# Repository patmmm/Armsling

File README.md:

About
=====

This is a "simple", but complete example of how to utilize WebRTC to do peer to
peer voice and video chatting between two or more people.

### Server Side 
This example uses node.js and socket.io to create a "Signaling Server", which
runs on (or near) your web server to manage who should talk to who. The purpose
of the signaling server is to relay information between peers while you are
setting them up to talk directly to each other.

### Client Side
Included is `client.html` which contains all of the logic to connect to the
signaling server, join a virtual group chat channel, connect with peers, and
stream video and audio to all party members using the raw WebRTC API.

Running
=======

### Node.js signaling server
You'll need to install `node.js` as well as the `express` and `socket.io` libraries:
```
npm install -g socket.io express
```

Then simply run the signaling server:
```
node signaling-server.js
```

### Web server
You'll also probably want to host `client.html` on a web server somewhere. You'll need
to edit `client.html` and change `YOURSERVERNAMEHERE` to be the hostname or IP of 
the signaling server.

Note: you can also simply open the file locally instead of using a web server,
but at the time of writing this only firefox will let you access the
webcam/microphone from a file hosted off of your local machine.

### Running the sample
Now navigate to wherever you stuck `client.html` and you should be presented with
a dialog asking permission to access your microphone / webcam. Once accepted,
you should see a local stream appear on the page. Now open up the same page in
another browser, on the same computer or another, and watch as the magic of WebRTC takes
effect and both images and audio samples mysteriously move from one browser to the other.
Repeat with as many browsers as you dare.

Note: At the time of writing this, only firefox and chrome support WebRTC,
however both browsers support this on Windows, Linux, Mac, and Android, so lots
of fun can be had pointing everyones' phones, tablets, and laptops at that `client.html`
and bogging down your network with audio/video traffic.

Using things other than jQuery, node.js, and socket.io
=============================================
The choice of node.js and socket.io is based purely on my familiarity with them
and the fact that their fairly easy to understand even if you aren't familiar
with them. However, you can use any mechanisms you want for your signaling system, you
just need a way to exchange ICE candidates and session descriptions between
clients.

The use of jQuery is even less important, I just like using it for DOM
manipulation, and we only do that to add and remove the <video>/<audio>
elements in this demo. We don't use it at all for anything WebRTC specific in
this example.

Adapter.js
==========
You'll see `client.html` use `adapter.js`. This "library" just normalizes the
WebRTC API, which will only be necessary while WebRTC is making its way through
the standards process. Once everything is standardized and functions are
de-prefixed in the browsers, this won't be necessary anymore.
# Armsling

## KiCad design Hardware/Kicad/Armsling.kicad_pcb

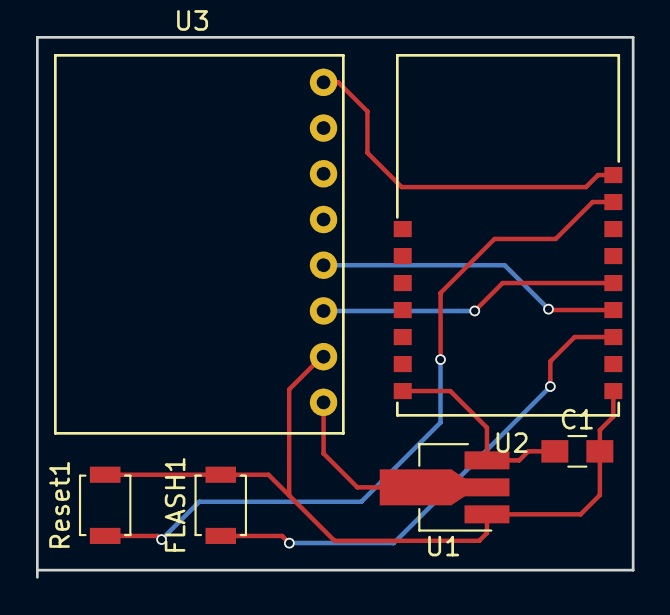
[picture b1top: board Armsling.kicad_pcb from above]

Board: 2 copper layers, 33.1 x 30.0 mm, 6 parts (0 on the bottom side), 8 nets.

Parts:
C1: 1 uF; C_0805_HandSoldering
FLASH1: SW_Push; SW_SPST_B3U-1000P
Reset1: SW_Push; SW_SPST_B3U-1000P
U1: XC6206P332PR; SOT-89-3_Handsoldering
U2: ESP8285_M2; ESP8285-M2
U3: MPU6050-GY521; MPU6050

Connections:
+BATT: U1.2, U3.1
GND: C1.2, FLASH1.2, Reset1.2, U1.1, U2.8, U3.2
unnamed: C1.1, U1.3, U2.7
unnamed: FLASH1.1, U2.10
unnamed: Reset1.1, U2.15
unnamed: U2.11, U3.4
unnamed: U2.12, U3.3
unnamed: U2.16, U3.8

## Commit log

2018-06-28 starto
2018-06-28 2nd cube added
2018-06-28 Axis defined
2018-06-30 Setup project react express webpack
2018-07-01 Completed config React
2018-07-01 playback.ejs
2018-07-01 Playback
2018-07-01 Let the HW begin
2018-07-01 Create HW folder
2018-07-01 remove unnecessary file
2018-08-06 make it better
2018-08-08 test upload
